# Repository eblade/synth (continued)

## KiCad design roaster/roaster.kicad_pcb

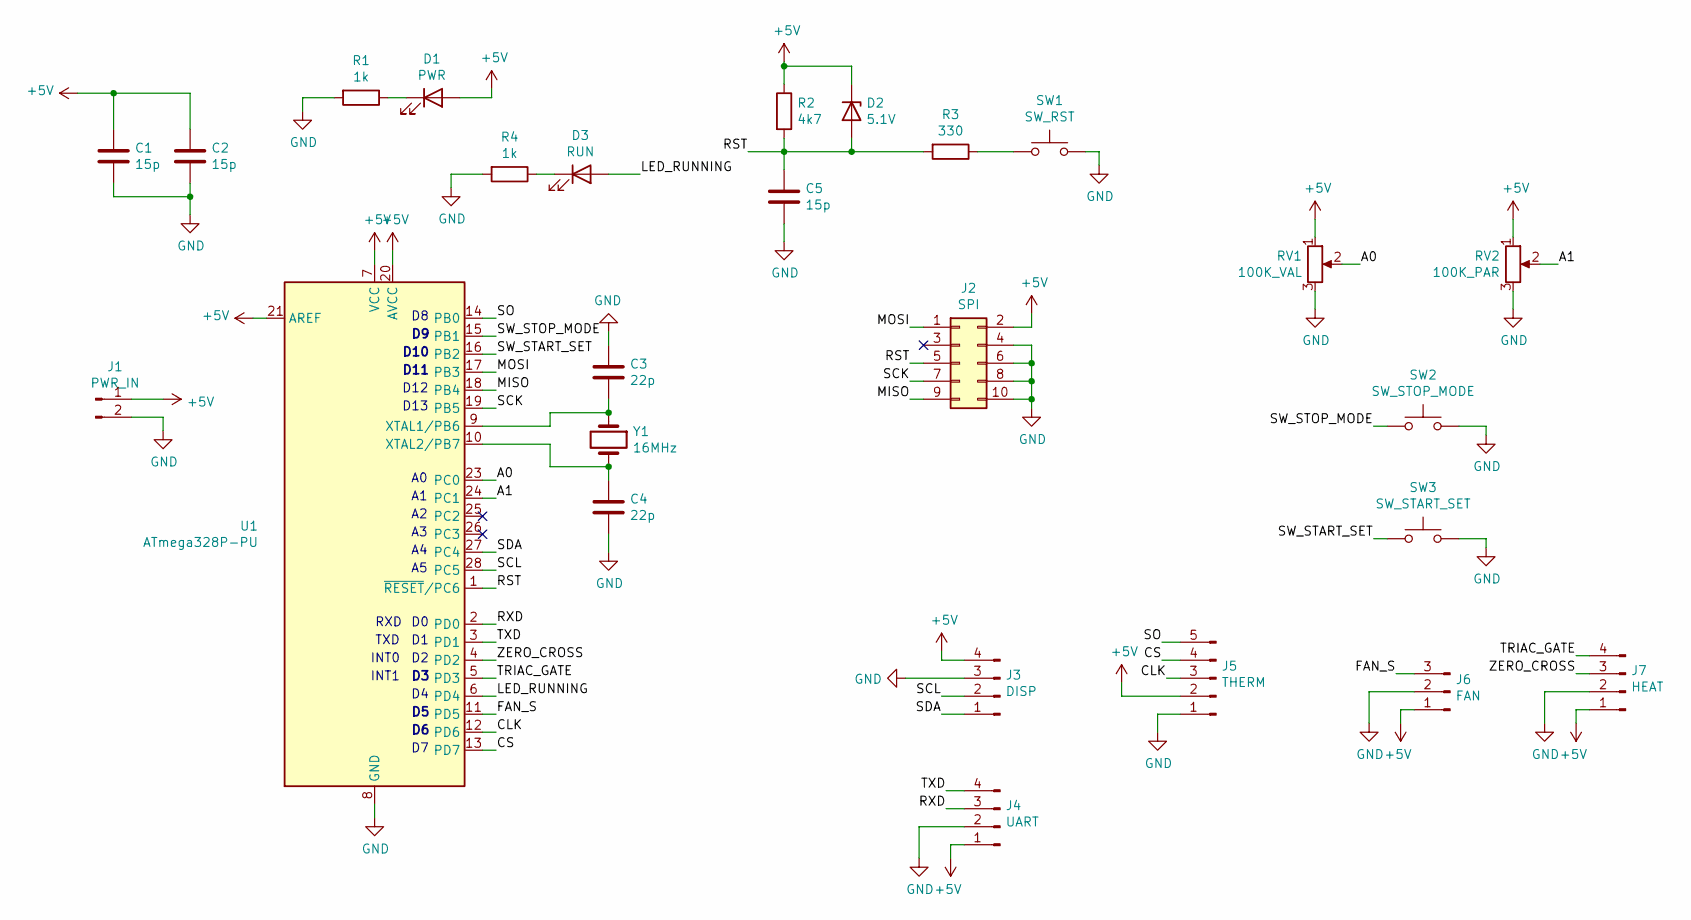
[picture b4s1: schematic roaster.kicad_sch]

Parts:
C1, C2, C5: 15p; C_Disc_D3.0mm_W1.6mm_P2.50mm
C3, C4: 22p; C_Disc_D3.0mm_W1.6mm_P2.50mm
D1: PWR; LED_D3.0mm
D2: 5.1V; D_A-405_P7.62mm_Horizontal
D3: RUN; LED_D3.0mm
J1: PWR_IN; PinHeader_1x02_P2.54mm_Vertical
J2: SPI; PinHeader_2x05_P2.54mm_Vertical
J3: DISP; PinHeader_1x04_P2.54mm_Vertical
J4: UART; PinHeader_1x04_P2.54mm_Vertical
J5: THERM; PinHeader_1x05_P2.54mm_Vertical
J6: FAN; PinHeader_1x03_P2.54mm_Vertical
J7: HEAT; PinHeader_1x04_P2.54mm_Vertical
R1, R4: 1k; R_Axial_DIN0204_L3.6mm_D1.6mm_P7.62mm_Horizontal
R2: 4k7; R_Axial_DIN0204_L3.6mm_D1.6mm_P7.62mm_Horizontal
R3: 330; R_Axial_DIN0204_L3.6mm_D1.6mm_P7.62mm_Horizontal
RV1: 100K_VAL; Potentiometer_Alps_RK09L_Single_Vertical
RV2: 100K_PAR; Potentiometer_Alps_RK09L_Single_Vertical
SW1: SW_RST; SW_PUSH_6mm_H4.3mm
SW2: SW_STOP_MODE; SW_PUSH_6mm_H4.3mm
SW3: SW_START_SET; SW_PUSH_6mm_H4.3mm
U1: ATmega328P-PU; DIP-28_W7.62mm
Y1: 16MHz; Crystal_HC18-U_Vertical

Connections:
+5V: C1.2, C2.2, D1.2 (A), D2.1 (K), J1.1, J2.2, J3.4, J4.1, J5.2, J6.1, J7.1, R2.1, RV1.1, RV2.1, U1.7 (VCC), U1.20 (AVCC), U1.21 (AREF)
/A0: RV1.2, U1.23 (PC0)
/A1: RV2.2, U1.24 (PC1)
/CLK: J5.3, U1.12 (PD6)
/CS: J5.4, U1.13 (PD7)
/FAN_S: J6.3, U1.11 (PD5)
/LED_RUNNING: D3.2 (A), U1.6 (PD4)
/MISO: J2.9, U1.18 (PB4)
/MOSI: J2.1, U1.17 (PB3)
/RST: C5.2, D2.2 (A), J2.5, R2.2, R3.2, U1.1 (~RESET/PC6)
/RXD: J4.3, U1.2 (PD0)
/SCK: J2.7, U1.19 (PB5)
/SCL: J3.2, U1.28 (PC5)
/SDA: J3.1, U1.27 (PC4)
/SO: J5.5, U1.14 (PB0)
/SW_START_SET: SW3.1, U1.16 (PB2)
/SW_STOP_MODE: SW2.1, U1.15 (PB1)
/TRIAC_GATE: J7.4, U1.5 (PD3)
/TXD: J4.4, U1.3 (PD1)
/ZERO_CROSS: J7.3, U1.4 (PD2)
GND: C1.1, C2.1, C3.1, C4.2, C5.1, J1.2, J2.4, J2.6, J2.8, J2.10, J3.3, J4.2, J5.1, J6.2, J7.2, R1.2, R4.2, RV1.3, RV2.3, SW1.2, SW2.2, SW3.2, U1.8 (GND), U1.22 (GND)
unnamed: C3.2, U1.9 (XTAL1/PB6), Y1.1
unnamed: C4.1, U1.10 (XTAL2/PB7), Y1.2
unnamed: D1.1 (K), R1.1
unnamed: D3.1 (K), R4.1
unnamed: R3.1, SW1.1

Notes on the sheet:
D12
D10
RXD
D13
D11
INT1
TXD
INT0

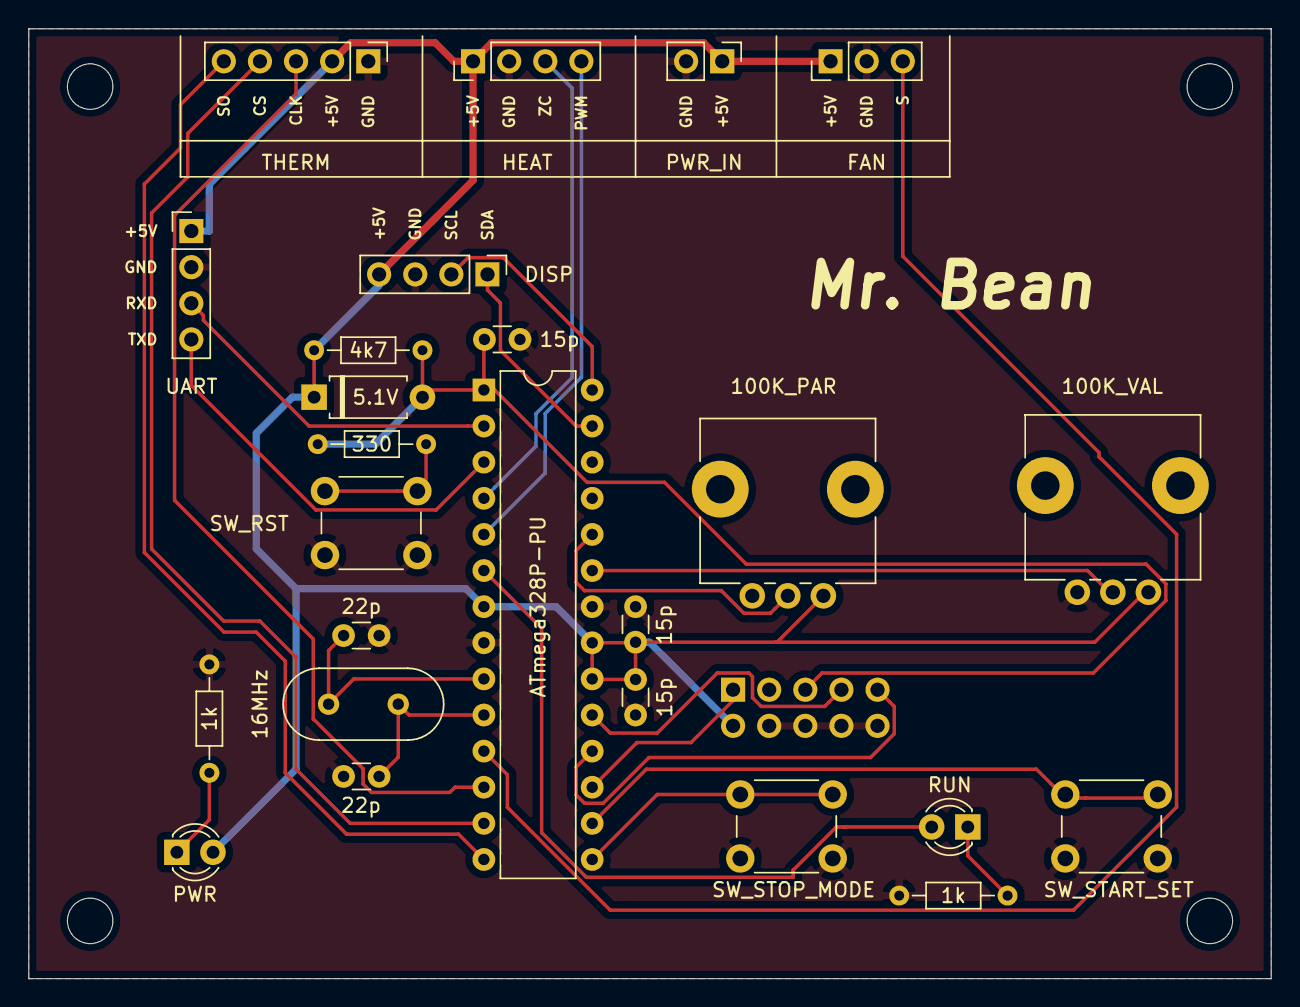
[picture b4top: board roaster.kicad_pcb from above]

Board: 2 copper layers, 87.4 x 66.8 mm, 26 parts (1 on the bottom side), 26 nets.
